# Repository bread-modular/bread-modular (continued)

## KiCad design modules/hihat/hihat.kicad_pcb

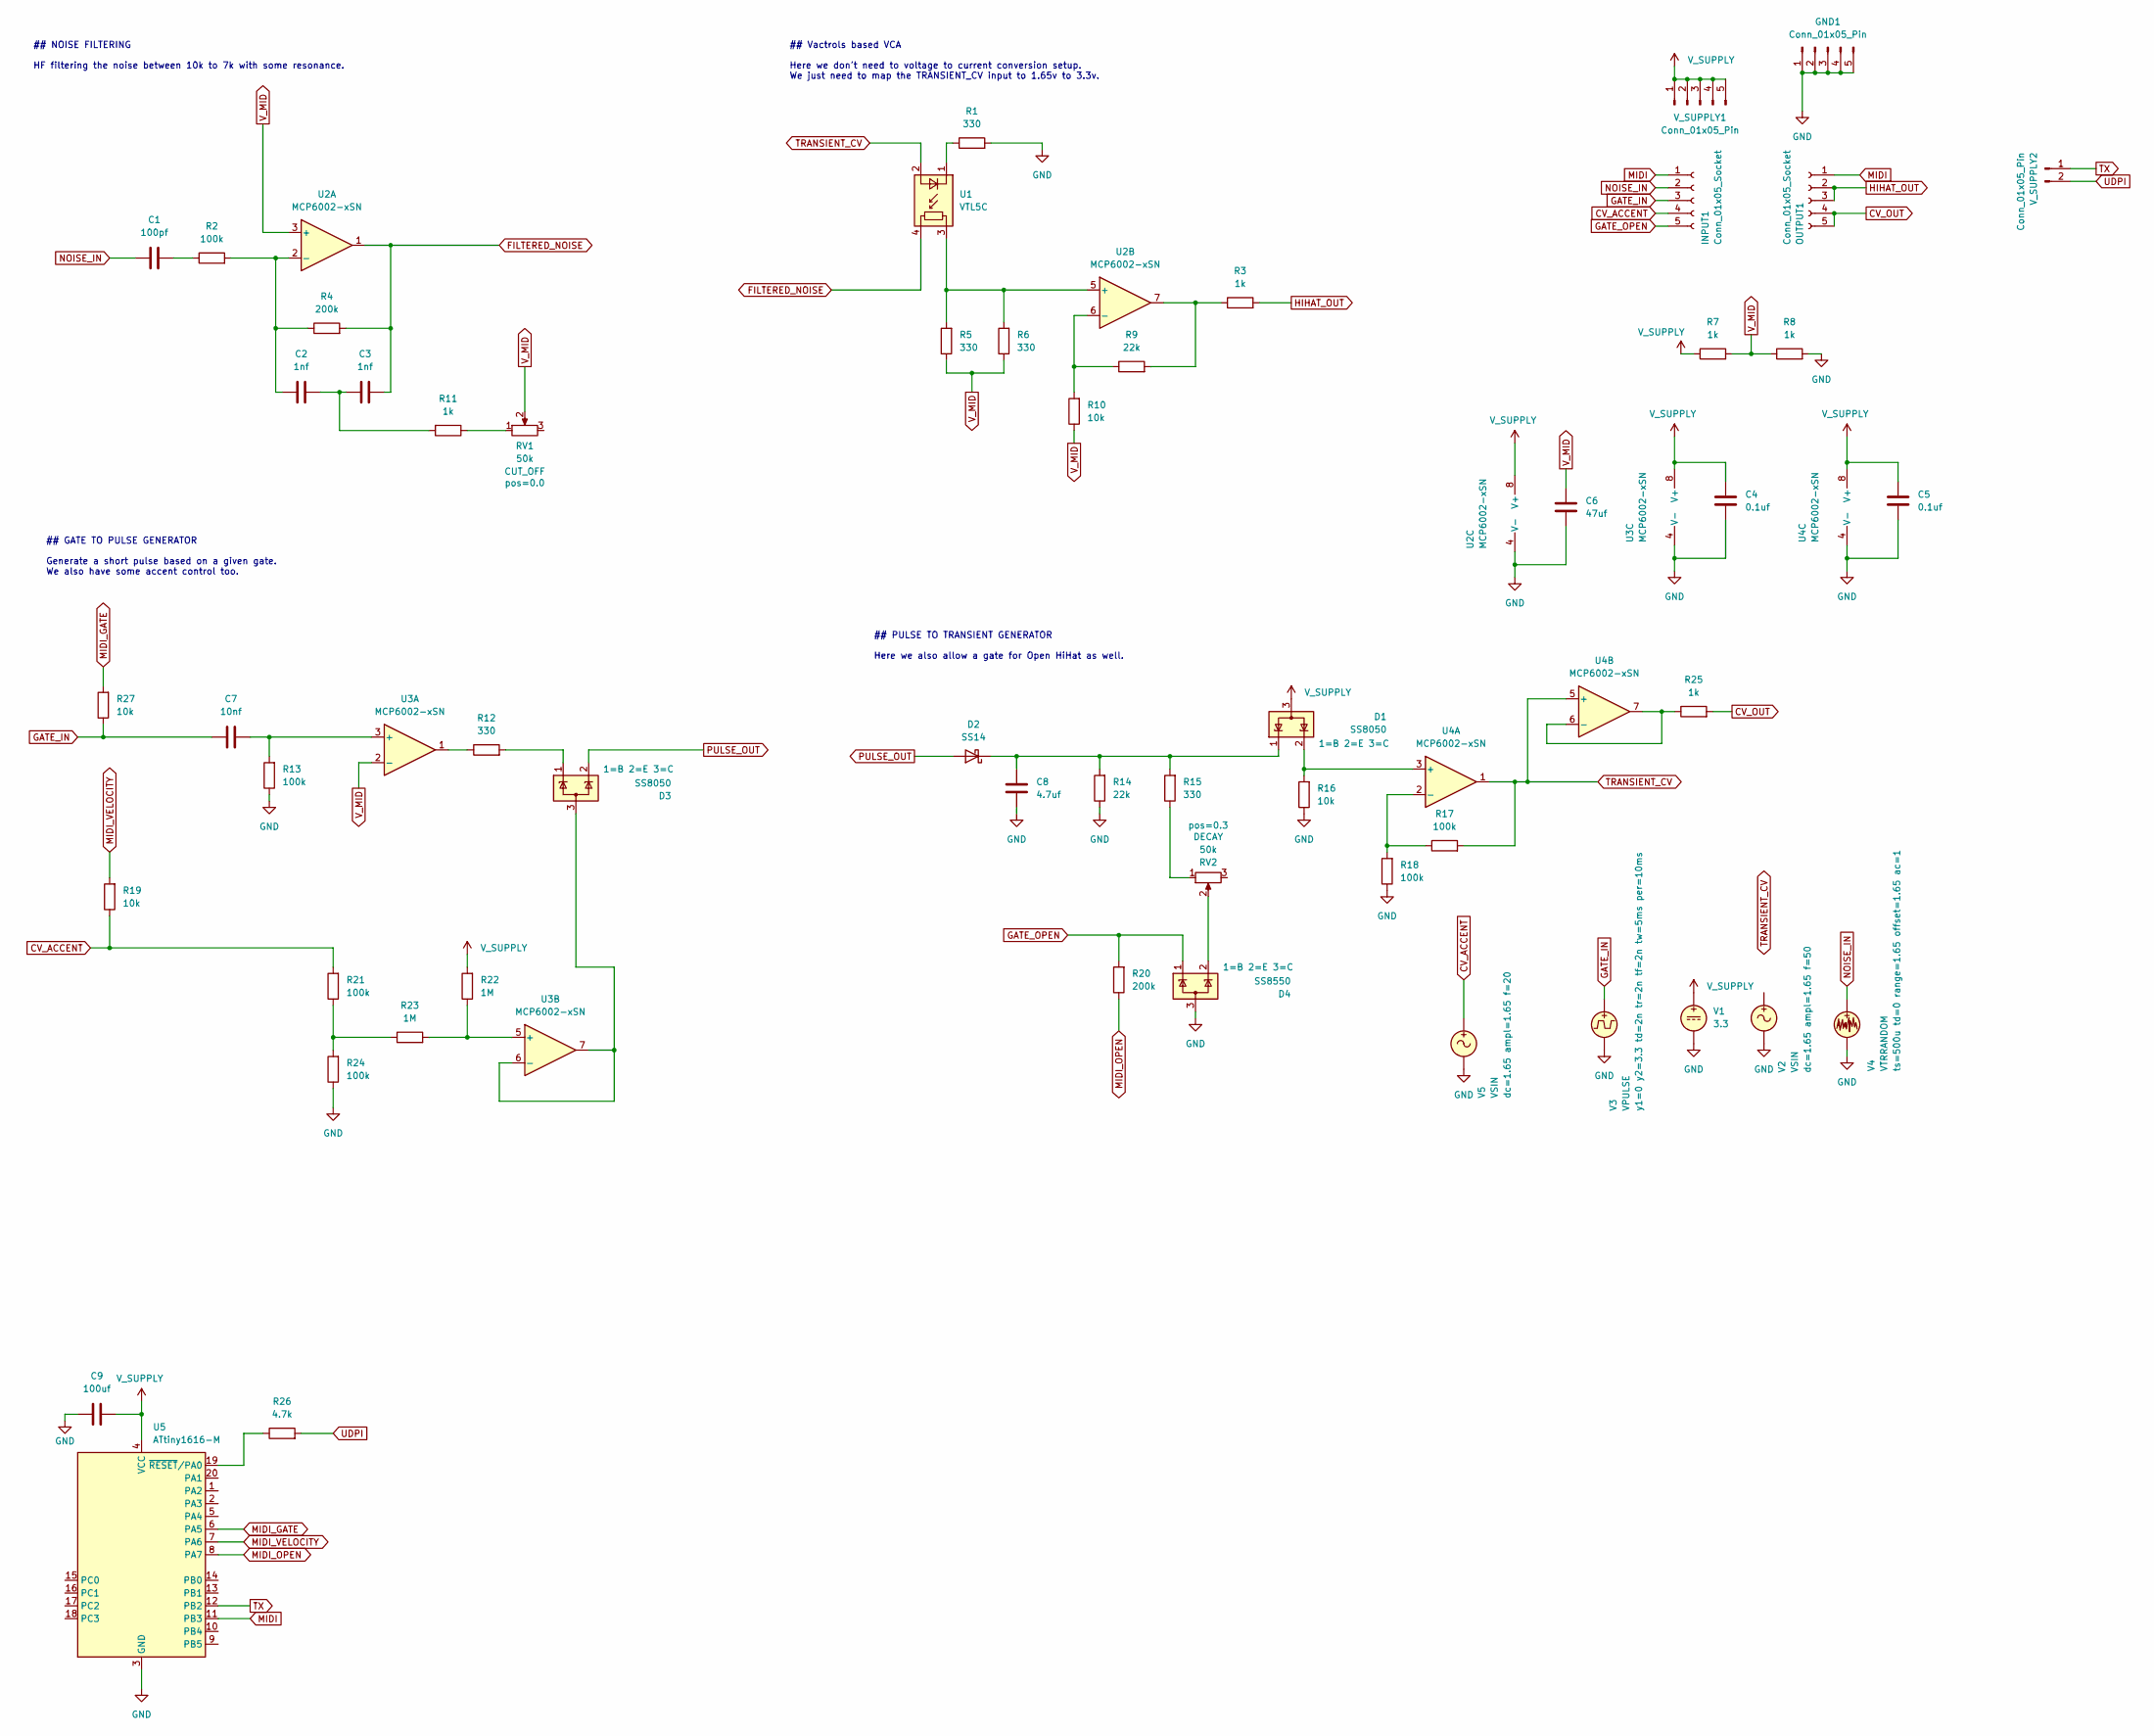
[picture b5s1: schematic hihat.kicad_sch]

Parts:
C1: 100pf; C_0402_1005Metric
C2, C3: 1nf; C_0402_1005Metric
C4, C5: 0.1uf; C_0402_1005Metric
C6: 47uf; C_0805_2012Metric
C7: 10nf; C_0402_1005Metric
C8: 4.7uf; C_0603_1608Metric
C9: 100uf; C_1206_3216Metric
D1, D3: SS8050; SOT-23
D2: SS14; D_SMA
D4: SS8550; SOT-23
GND1: Conn_01x05_Pin; Power_Connector
INPUT1: Conn_01x05_Socket; PinSocket_1x05_P2.54mm_Vertical
OUTPUT1: Conn_01x05_Socket; PinSocket_1x05_P2.54mm_Vertical
R1, R5, R6, R12, R15: 330; R_0402_1005Metric
R2, R13, R17, R18, R21, R24: 100k; R_0402_1005Metric
R3, R7, R8, R11, R25: 1k; R_0402_1005Metric
R4, R20: 200k; R_0402_1005Metric
R9, R14: 22k; R_0402_1005Metric
R10, R16, R19, R27: 10k; R_0402_1005Metric
R22, R23: 1M; R_0402_1005Metric
R26: 4.7k; R_0402_1005Metric
RV1, RV2: 50k; Potentiometer_RV09
U1: VTL5C
U2, U3, U4: MCP6002-xSN; SOIC-8-1EP_3.9x4.9mm_P1.27mm_EP2.29x3mm
U5: ATtiny1616-M; VQFN-20-1EP_3x3mm_P0.4mm_EP1.7x1.7mm
V1: 3.3
V2, V5: VSIN
V3: VPULSE
V4: VTRRANDOM
V_SUPPLY1: Conn_01x05_Pin; Power_Connector
V_SUPPLY2: Conn_01x05_Pin; Conn_Holes_2

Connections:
CV_ACCENT: INPUT1.4, R19.1, R21.2, V5.1
CV_OUT: OUTPUT1.4, OUTPUT1.5, R25.2
FILTERED_NOISE: C3.2, R4.2, U1.4, U2.1
GATE_IN: C7.1, INPUT1.3, R27.1, V3.1
GATE_OPEN: D4.1 (K), INPUT1.5, R20.2
GND: C4.1, C5.1, C6.1, C8.1, C9.1, D4.3 (A), GND1.1, GND1.2, GND1.3, GND1.4, GND1.5, R1.2, R8.2, R13.1, R14.1, R16.1, R18.1, R24.1, U2.4 (V-), U3.4 (V-), U4.4 (V-), U5.3 (GND), U5.21 (GND), V1.2, V2.2, V3.2, V4.2, V5.2
HIHAT_OUT: OUTPUT1.2, OUTPUT1.3, R3.2
MIDI: INPUT1.1, OUTPUT1.1, U5.11 (PB3)
MIDI_GATE: R27.2, U5.6 (PA5)
MIDI_OPEN: R20.1, U5.8 (PA7)
MIDI_VELOCITY: R19.2, U5.7 (PA6)
NOISE_IN: C1.1, INPUT1.2, V4.1
unnamed: C1.2, R2.1
unnamed: C2.2, C3.1, R11.2
unnamed: C8.2, D1.1 (K), D2.1 (K), R14.2, R15.2
unnamed: D3.3 (A), U3.6 (-), U3.7
unnamed: D3.1 (K), R12.2
unnamed: D4.2 (K), RV2.2
unnamed: R3.1, R9.2, U2.7
unnamed: R11.1, RV1.1
unnamed: R12.1, U3.1
unnamed: R15.1, RV2.1
unnamed: R21.1, R23.1, R24.2
unnamed: R1.1, U1.1 (-)
unnamed: C2.1, R2.2, R4.1, U2.2 (-)
unnamed: R5.2, R6.2, U1.3, U2.5 (+)
unnamed: R9.1, R10.2, U2.6 (-)
unnamed: C7.2, R13.2, U3.3 (+)
unnamed: R22.1, R23.2, U3.5 (+)
unnamed: D1.2 (K), R16.2, U4.3 (+)
unnamed: R17.1, R18.2, U4.2 (-)
unnamed: R25.1, U4.6 (-), U4.7
unnamed: R26.1, U5.19 (~RESET/PA0)
PULSE_OUT: D2.2 (A), D3.2 (K)
TRANSIENT_CV: R17.2, U1.2 (+), U4.1, U4.5 (+)
TX: U5.12 (PB2), V_SUPPLY2.1
UDPI: R26.2, V_SUPPLY2.2
V_MID: C6.2, R5.1, R6.1, R7.2, R8.1, R10.1, RV1.2, U2.3 (+), U3.2 (-)
V_SUPPLY: C4.2, C5.2, C9.2, D1.3 (A), R7.1, R22.2, U2.8 (V+), U3.8 (V+), U4.8 (V+), U5.4 (VCC), V1.1, V_SUPPLY1.1, V_SUPPLY1.2, V_SUPPLY1.3, V_SUPPLY1.4, V_SUPPLY1.5

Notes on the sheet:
## NOISE FILTERING HF filtering the noise between 10k to 7k with some resonance.
## Vactrols based VCA Here we don't need to voltage to current conversion setup. We just need to map the TRANSIENT_CV input to 1.65v to 3.3v.
## GATE TO PULSE GENERATOR Generate a short pulse based on a given gate. We also have some accent control too.
## PULSE TO TRANSIENT GENERATOR Here we also allow a gate for Open HiHat as well.

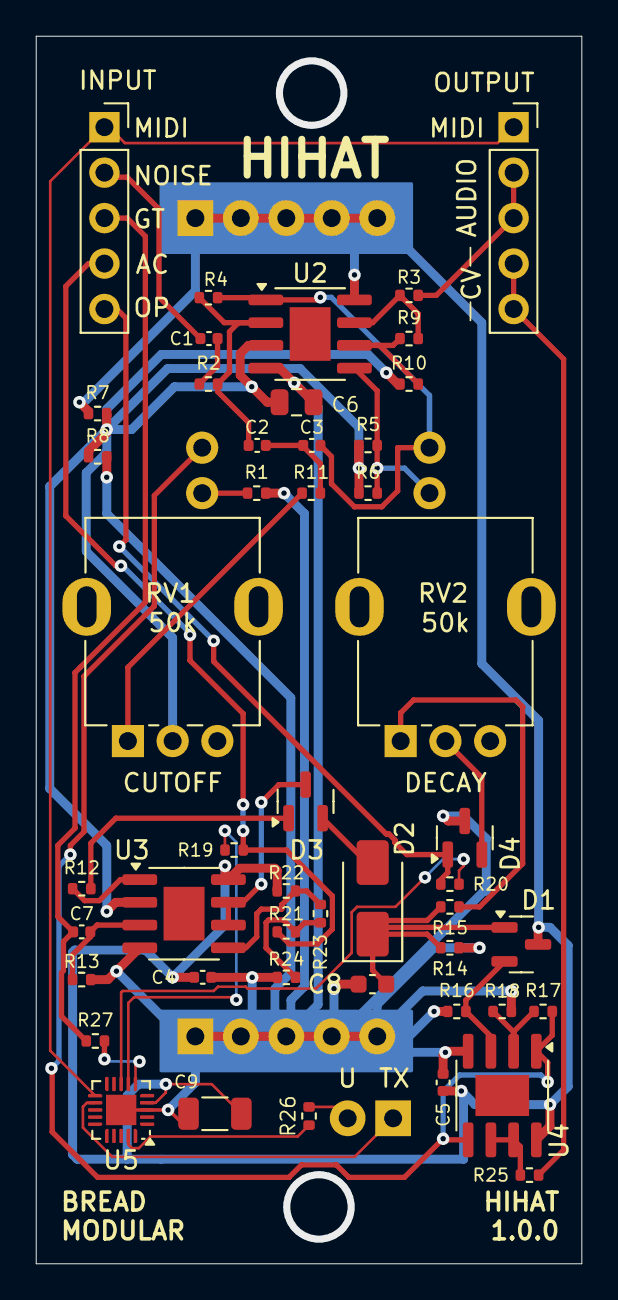
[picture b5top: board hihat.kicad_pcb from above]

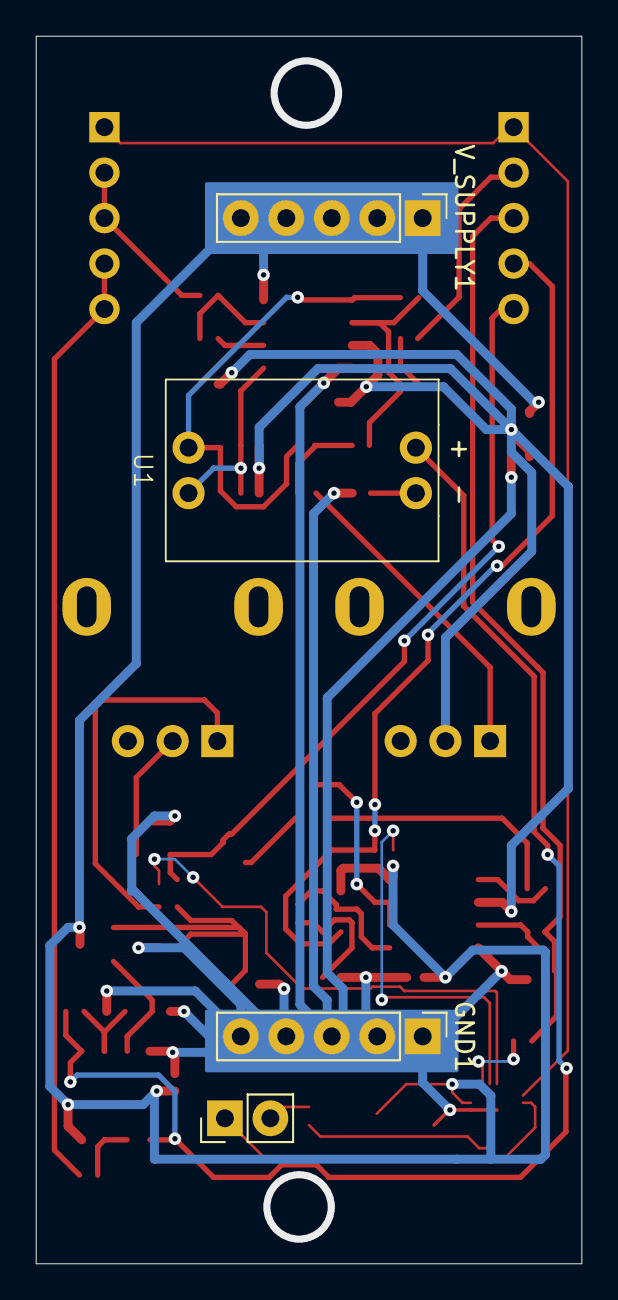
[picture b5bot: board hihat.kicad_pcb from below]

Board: 2 copper layers, 30.5 x 68.6 mm, 52 parts (4 on the bottom side), 39 nets.

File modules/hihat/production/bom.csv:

Designator,Footprint,Quantity,Value,LCSC Part #
C1,0402,1,100pf,
"C2, C3",0402,2,1nf,
"C4, C5",0402,2,0.1uf,
C6,0805,1,47uf,
C7,0402,1,10nf,
C8,0603,1,4.7uf,
C9,1206,1,100uf,
"D1, D3",SOT-23,2,SS8050,
D2,D_SMA,1,SS14,
D4,SOT-23,1,SS8550,
"GND1, V_SUPPLY1",Power_Connector,2,Conn_01x05_Pin,
"INPUT1, OUTPUT1",PinSocket_1x05_P2.54mm_Vertical,2,Conn_01x05_Socket,
"R1, R12, R15, R5, R6",0402,5,330,
"R10, R16, R19, R27",0402,4,10k,
"R11, R25, R3, R7, R8",0402,5,1k,
"R13, R17, R18, R2, R21, R24",0402,6,100k,
"R14, R9",0402,2,22k,
"R20, R4",0402,2,200k,
"R22, R23",0402,2,1M,
R26,0402,1,4.7k,
"RV1, RV2",Potentiometer_RV09,2,50k,
U1,VTL5C,1,VTL5C,
"U2, U3, U4",SOIC-8-1EP_3.9x4.9mm_P1.27mm_EP2.29x3mm,3,MCP6002-xSN,
U5,VQFN-20-1EP_3x3mm_P0.4mm_EP1.7x1.7mm,1,ATtiny1616-M,
V_SUPPLY2,Conn_Holes_2,1,Conn_01x05_Pin,

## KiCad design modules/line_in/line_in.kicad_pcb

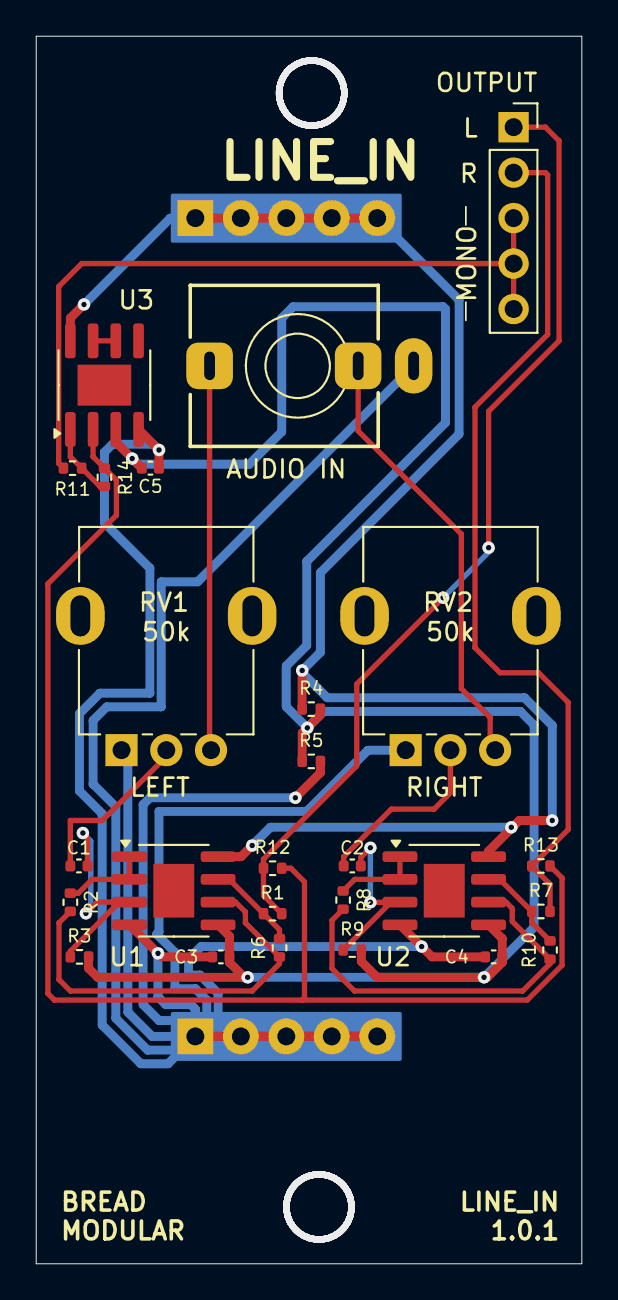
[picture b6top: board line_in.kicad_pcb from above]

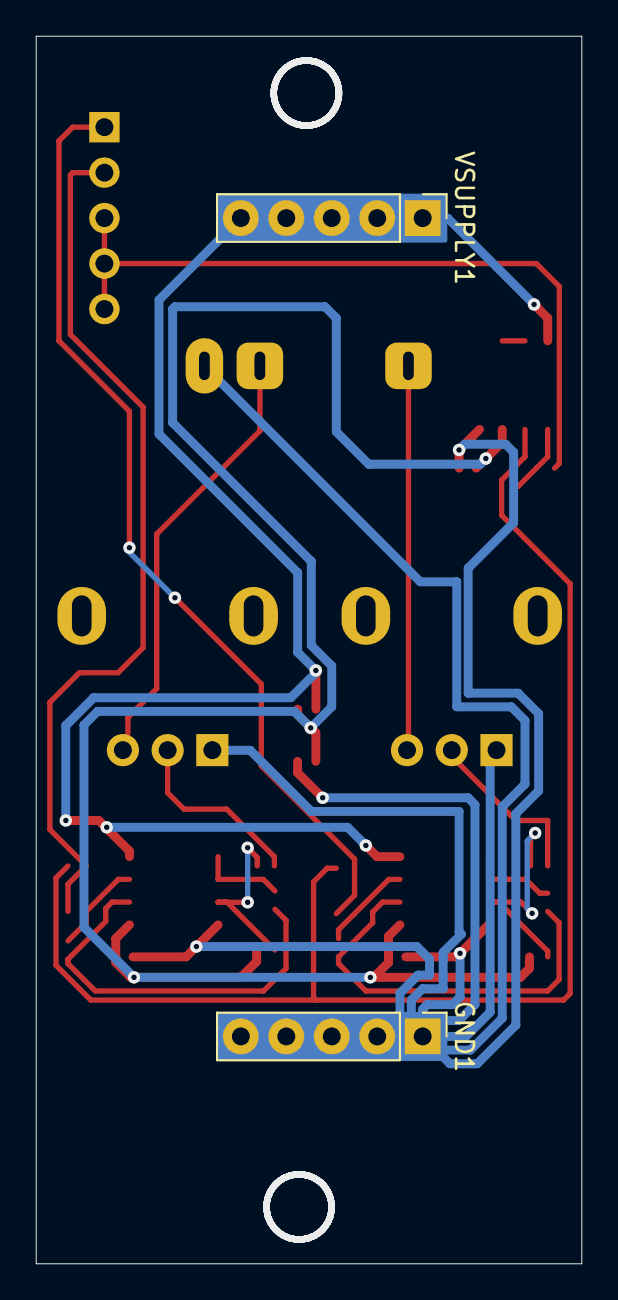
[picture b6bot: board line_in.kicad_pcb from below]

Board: 2 copper layers, 30.5 x 68.6 mm, 28 parts (2 on the bottom side), 21 nets.

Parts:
C1, C2, C3, C4, C5: 0.1uf; C_0402_1005Metric
GND1: Conn_01x05_Pin; Power_Connector
J1: AudioJack3; Jack_3.5mm_QingPu_WQP-PJ366ST_Vertical
OUTPUT1: Conn_01x05_Socket; PinSocket_1x05_P2.54mm_Vertical
R1, R4, R5, R7, R11: 1k; R_0402_1005Metric
R2, R8: 22k; R_0402_1005Metric
R3, R9: 1M; R_0402_1005Metric
R6, R10, R12, R13: 100k; R_0402_1005Metric
R14: 51k; R_0402_1005Metric
RV1, RV2: 50k; Potentiometer_RV09
U1, U2, U3: MCP6002-xSN; SOIC-8-1EP_3.9x4.9mm_P1.27mm_EP2.29x3mm
VSUPPLY1: Conn_01x05_Pin; Power_Connector

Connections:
GND: C3.1, C4.1, C5.1, GND1.1, GND1.2, GND1.3, GND1.4, GND1.5, J1.S, R5.2, RV1.1, RV2.1, U1.4 (V-), U2.4 (V-), U3.4 (V-)
IN_L: J1.T, RV1.3
IN_R: J1.R, RV2.3
unnamed: C1.1, RV1.2
unnamed: C2.1, RV2.2
unnamed: R1.1, R6.2, U1.7
unnamed: R7.1, R10.2, U2.7
unnamed: R11.1, R14.2, U3.1
unnamed: C1.2, R3.1, U1.3 (+)
unnamed: R2.1, U1.1, U1.2 (-)
unnamed: R2.2, R6.1, U1.6 (-)
unnamed: C2.2, R9.1, U2.3 (+)
unnamed: R8.1, U2.1, U2.2 (-)
unnamed: R8.2, R10.1, U2.6 (-)
unnamed: R12.2, R13.2, R14.1, U3.2 (-)
unnamed: U3.6 (-), U3.7
OUT_L: OUTPUT1.1, R1.2, R12.1
OUT_MONO: OUTPUT1.3, OUTPUT1.4, OUTPUT1.5, R11.2
OUT_R: OUTPUT1.2, R7.2, R13.1
V_MID: C3.2, C4.2, C5.2, R3.2, R4.2, R5.1, R9.2, U1.5 (+), U2.5 (+), U3.3 (+)
V_SUPLY: R4.1, U1.8 (V+), U2.8 (V+), U3.8 (V+), VSUPPLY1.1, VSUPPLY1.2, VSUPPLY1.3, VSUPPLY1.4, VSUPPLY1.5

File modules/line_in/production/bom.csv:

Designator,Footprint,Quantity,Value,LCSC Part #
"C1, C2, C3, C4, C5",0402,5,0.1uf,
"GND1, VSUPPLY1",Power_Connector,2,Conn_01x05_Pin,
J1,Jack_3.5mm_QingPu_WQP-PJ366ST_Vertical,1,AudioJack3,
OUTPUT1,PinSocket_1x05_P2.54mm_Vertical,1,Conn_01x05_Socket,
"R1, R11, R4, R5, R7",0402,5,1k,
"R10, R12, R13, R6",0402,4,100k,
R14,0402,1,51k,
"R2, R8",0402,2,22k,
"R3, R9",0402,2,1M,
"RV1, RV2",Potentiometer_RV09,2,50k,
"U1, U2, U3",SOIC-8-1EP_3.9x4.9mm_P1.27mm_EP2.29x3mm,3,MCP6002-xSN,C7377

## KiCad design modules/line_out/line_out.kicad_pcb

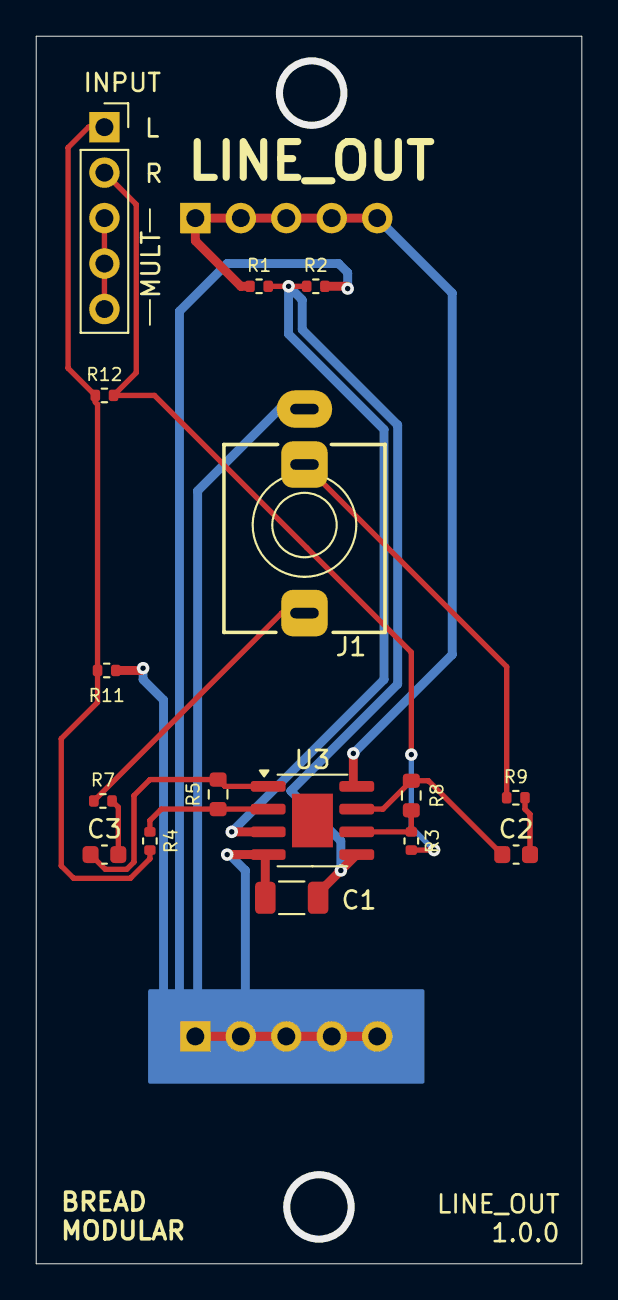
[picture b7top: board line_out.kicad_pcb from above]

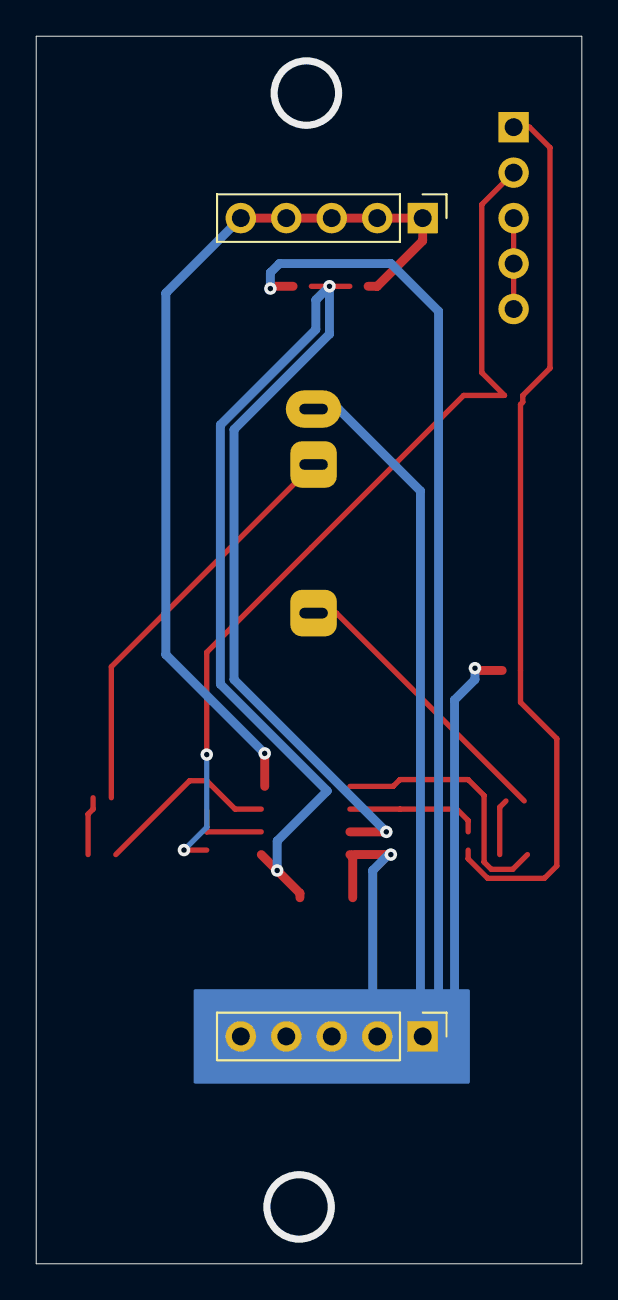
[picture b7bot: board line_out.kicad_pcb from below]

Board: 2 copper layers, 30.5 x 68.6 mm, 18 parts (2 on the bottom side), 14 nets.

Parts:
5V1: Conn_01x05_Pin; PinHeader_1x05_P2.54mm_Vertical
C1: 100uf; C_1206_3216Metric
C2, C3: 4.7uf; C_0603_1608Metric
GND1: Conn_01x05_Pin; PinHeader_1x05_P2.54mm_Vertical
INPUT1: Conn_01x05_Socket; PinSocket_1x05_P2.54mm_Vertical
J1: LineOut; Jack_3.5mm_QingPu_WQP-PJ366ST_Vertical
R1, R2, R7, R9: 1k; R_0402_1005Metric
R3, R4: 1M; R_0402_1005Metric
R5, R8: 330k; R_0603_1608Metric
R11, R12: 10k; R_0402_1005Metric
U3: MCP6002-xSN; SOIC-8-1EP_3.9x4.9mm_P1.27mm_EP2.29x3mm

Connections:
+2.5V: C1.2, R1.2, R2.1, U3.3 (+), U3.5 (+)
GND: C1.1, GND1.1, GND1.2, GND1.3, GND1.4, GND1.5, J1.S, R2.2, R11.2, U3.4 (V-)
IN_L: INPUT1.1, R4.2, R11.1, R12.1
IN_R: INPUT1.2, R3.2, R12.2
unnamed: C2.1, R8.1, U3.7
unnamed: C2.2, R9.2
unnamed: C3.1, R5.1, U3.1
unnamed: C3.2, R7.2
unnamed: INPUT1.3, INPUT1.4, INPUT1.5
unnamed: R4.1, R5.2, U3.2 (-)
unnamed: R3.1, R8.2, U3.6 (-)
OUT_L: J1.T, R7.1
OUT_R: J1.R, R9.1
V_SUPPLY: 5V1.1, 5V1.2, 5V1.3, 5V1.4, 5V1.5, R1.1, U3.8 (V+)

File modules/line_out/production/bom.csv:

Designator,Footprint,Quantity,Value,LCSC Part #
"5V1, GND1",PinHeader_1x05_P2.54mm_Vertical,2,Conn_01x05_Pin,
C1,1206,1,100uf,
"C2, C3",0603,2,4.7uf,
INPUT1,PinSocket_1x05_P2.54mm_Vertical,1,Conn_01x05_Socket,
J1,Jack_3.5mm_QingPu_WQP-PJ366ST_Vertical,1,LineOut,
"R1, R2, R7, R9",0402,4,1k,
"R11, R12",0402,2,10k,
"R3, R4",0402,2,1M,
"R5, R8",0603,2,330k,
U3,SOIC-8-1EP_3.9x4.9mm_P1.27mm_EP2.29x3mm,1,MCP6002-xSN,
